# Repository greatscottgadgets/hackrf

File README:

This repository contains hardware designs and software for HackRF, a project to
produce a low cost, open source software radio platform.

https://github.com/wishi/hackrf/raw/master/doc/lemonAndjelly.jpeg

principal author: Michael Ossmann <mike@ossmann.com>
source repository: https://github.com/mossmann/hackrf

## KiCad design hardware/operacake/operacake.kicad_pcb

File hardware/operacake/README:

Copyright 2012 - 2016 Great Scott Gadgets

These files are part of HackRF.

This is a free hardware design; you can redistribute it and/or modify
it under the terms of the GNU General Public License as published by
the Free Software Foundation; either version 2, or (at your option)
any later version.

This design is distributed in the hope that it will be useful,
but WITHOUT ANY WARRANTY; without even the implied warranty of
MERCHANTABILITY or FITNESS FOR A PARTICULAR PURPOSE.  See the
GNU General Public License for more details.

You should have received a copy of the GNU General Public License
along with this design; see the file COPYING.  If not, write to
the Free Software Foundation, Inc., 51 Franklin Street,
Boston, MA 02110-1301, USA.

Opera Cake is an RF switching add-on for HackRF One.

hardware notes:

Schematic and layout files were designed in KiCad, an open source electronic
design automation package.

order of copper layers:
    Copper 1:  C1F (front)
    Copper 2:  C2
    Copper 3:  C3
    Copper 4:  C4B (back)

PCB description: 4 layer PCB 0.0646 in
    Copper       1:  1 oz copper (1.4 mil)
    Dielectric 1-2:  6.7 mil prepreg
    Copper       2:  0.5 oz copper (0.7 mil)
    Dielectric 2-3:  47 mil core
    Copper       3:  0.5 oz copper (0.7 mil)
    Dielectric 3-4:  6.7 mil prepreg
    Copper       4:  1 oz copper (1.4 mil)

FR408 or similar substrate with Er=3.66 (+/- 0.1)
double side solder mask green
double side silkscreen white
6 mil min trace width and
6 mil min isolation

PCBs of this specification are available from OSH Park.

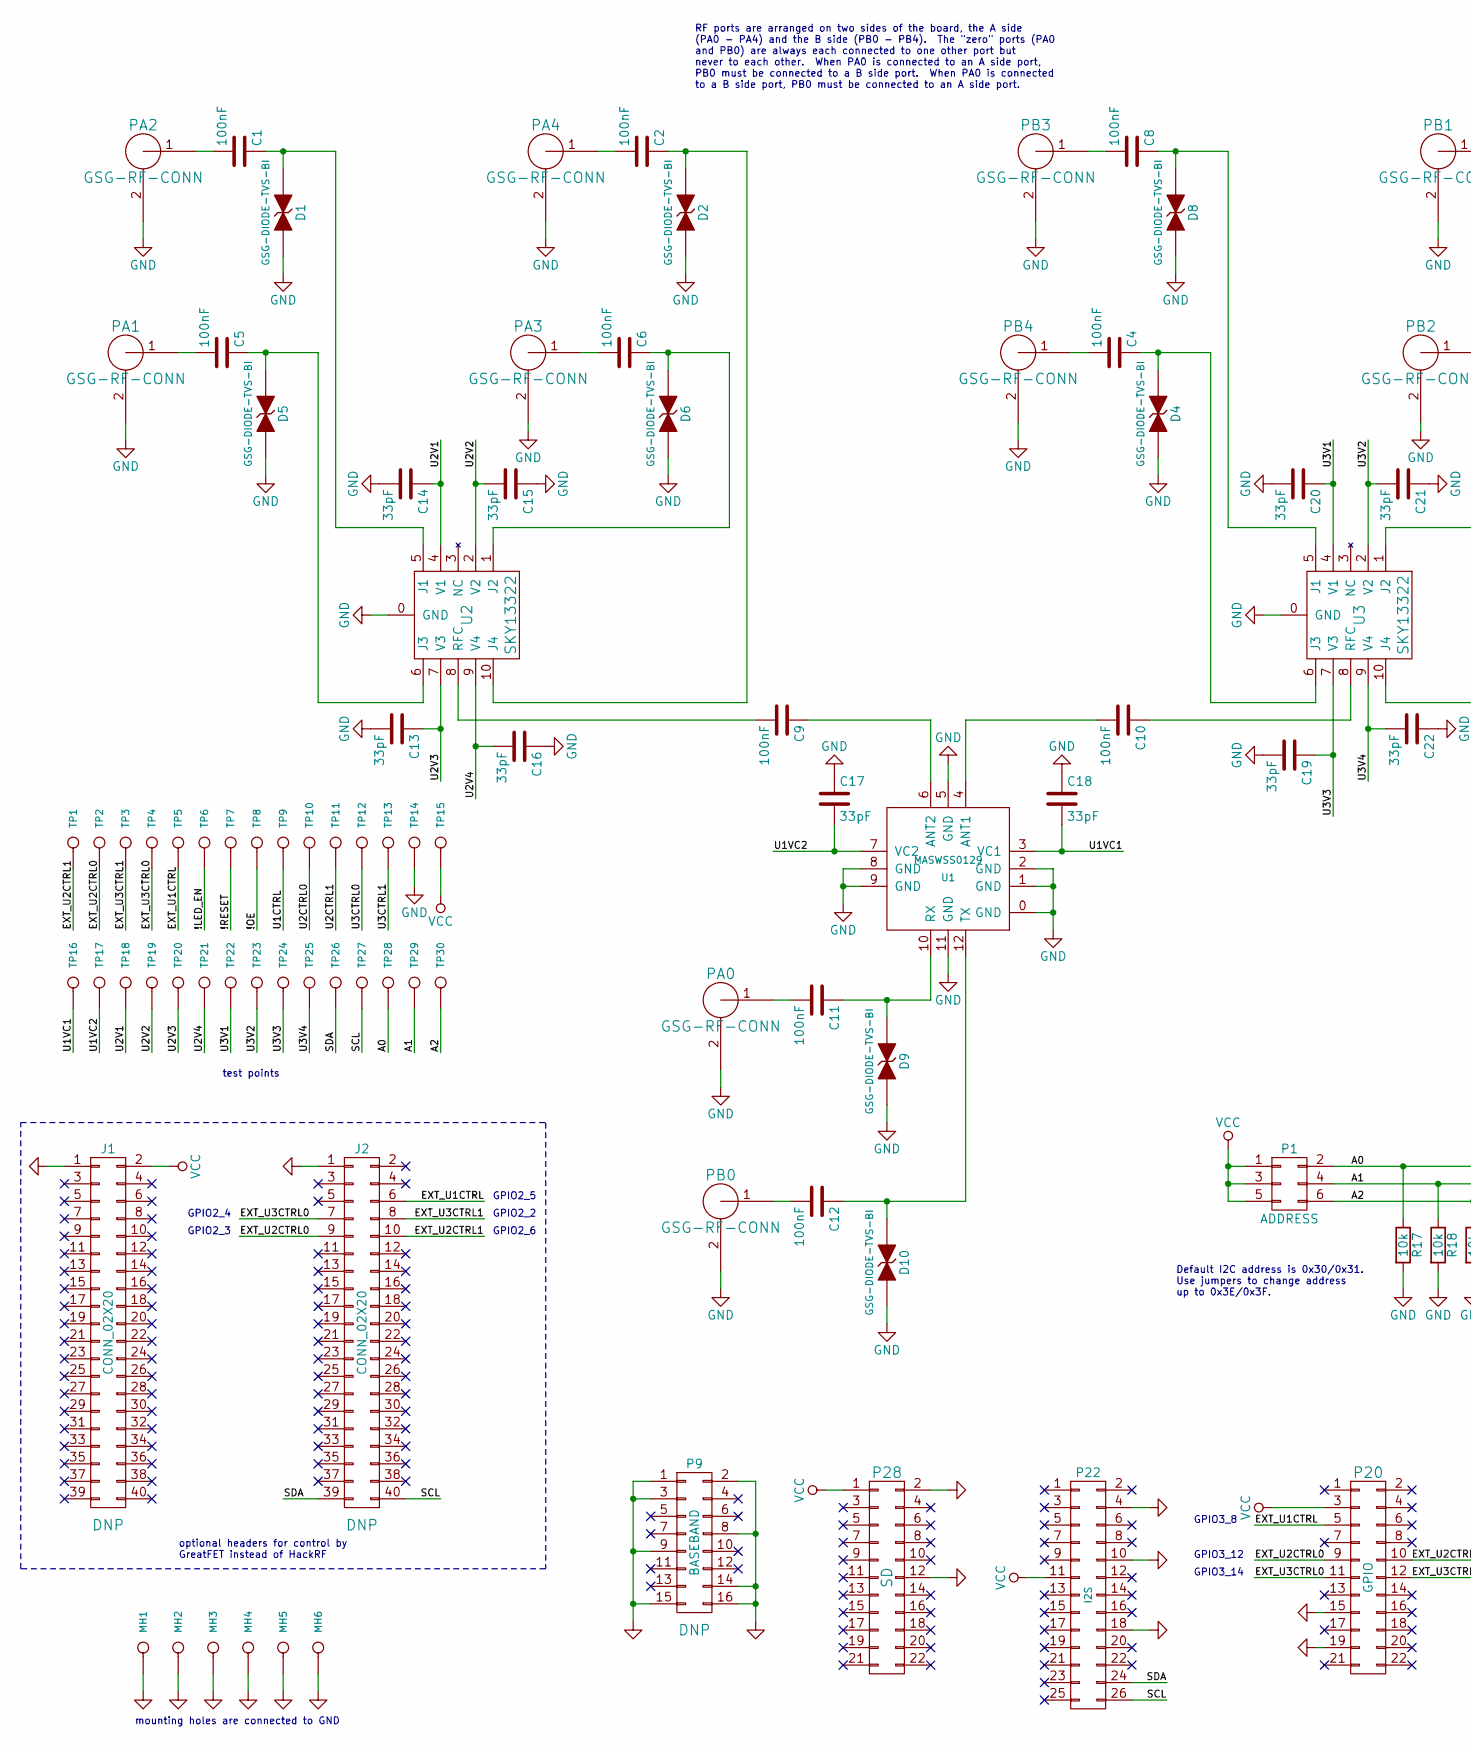
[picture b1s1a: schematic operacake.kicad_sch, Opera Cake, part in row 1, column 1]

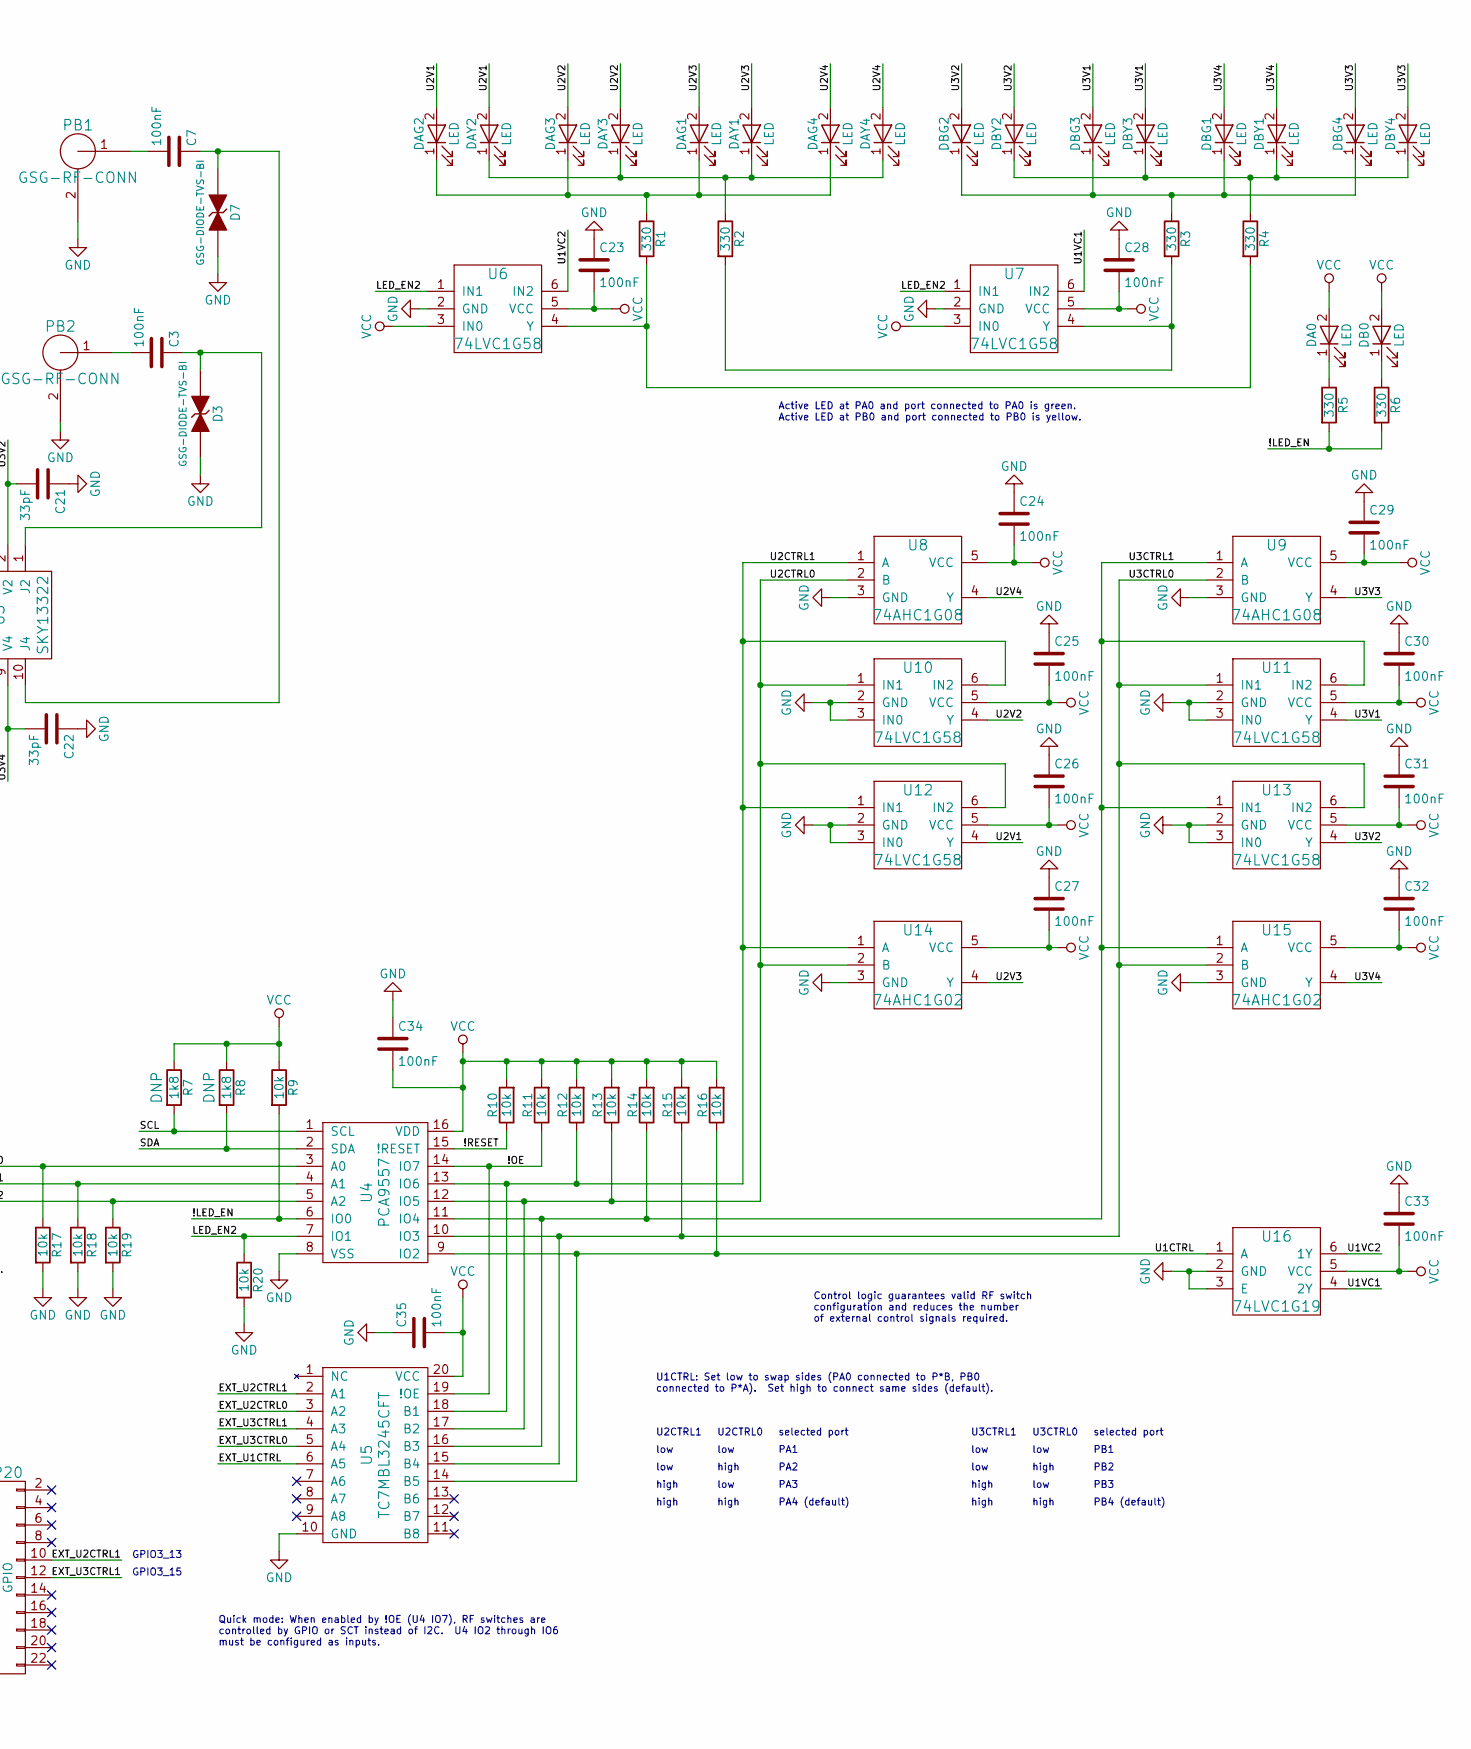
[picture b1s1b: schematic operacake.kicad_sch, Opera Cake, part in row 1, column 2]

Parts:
C1, C2, C3, C4, C5, C6, C7, C8, C9, C10, C11, C12, C23, C24, C25, C26, C27, C28, C29, C30, C31, C32, C33, C34, C35: 100nF; 0402; Part Number GRM155R61A104KA01D
C13, C14, C15, C16, C17, C18, C19, C20, C21, C22: 33pF; 0402; Part Number GRM1555C1H330JA01D
D1, D2, D3, D4, D5, D6, D7, D8, D9, D10: GSG-DIODE-TVS-BI; 0402; Part Number LXES15AAA1-153
DA0: LED; 0603D; Part Number SML-LX0603GW-TR
DAG1, DAG2, DAG3, DAG4: LED; 0603D; Part Number SML-LX0603GW-TR
DAY1, DAY2, DAY3, DAY4: LED; 0603D; Part Number SML-LX0603YW-TR
DB0: LED; 0603D; Part Number SML-LX0603YW-TR
DBG1, DBG2, DBG3, DBG4: LED; 0603D; Part Number SML-LX0603GW-TR
DBY1, DBY2, DBY3, DBY4: LED; 0603D; Part Number SML-LX0603YW-TR
J1, J2: CONN_02X20; HEADER-2x20-REVERSE
MH1, MH2, MH3, MH4, MH5, MH6: MOUNTING_HOLE; HOLE126MIL-COPPER
P1: ADDRESS; HEADER-2x3; Part Number XG8T-0631
P9: BASEBAND; HEADER-2x8; Part Number SSQ-108-03-G-D
P20: GPIO; HEADER-2x11; Part Number SSQ-111-03-G-D
P22: I2S; HEADER-2x13; Part Number SSQ-113-03-G-D
P28: SD; HEADER-2x11; Part Number SSQ-111-03-G-D
PA0, PA1, PA2, PA3, PA4: GSG-RF-CONN; GSG-SMA-73251-2120; Part Number 73251-2121
PB0, PB1, PB2, PB3, PB4: GSG-RF-CONN; GSG-SMA-73251-2120; Part Number 73251-2121
R1, R2, R3, R4, R5, R6: 330; 0603; Part Number RMCF0603JT330R
R7, R8: 1k8; 0603
R9, R10, R11, R12, R13, R14, R15, R16, R17, R18, R19, R20: 10k; 0603; Part Number ERJ-3GEYJ103V
TP1, TP2, TP3, TP4, TP5, TP6, TP7, TP8, TP9, TP10, TP11, TP12, TP13, TP14, TP15, TP16, TP17, TP18, TP19, TP20, TP21, TP22, TP23, TP24, TP25, TP26, TP27, TP28, TP29, TP30: CONN_1; TESTPOINT-50MIL
U1: MASWSS0129; QFN12-3; Part Number MASWSS0129TR-3000
U2, U3: SKY13322; SKY13322-375LF; Part Number SKY13322-375LF
U4: PCA9557; TSSOP16; Part Number PCA9557PW,118
U5: TC7MBL3245CFT; TSSOP20; Part Number TC7MBL3245CFT(EL)
U6, U7, U10, U11, U12, U13: 74LVC1G58; SOT363; Part Number 74LVC1G58DW-7
U8, U9: 74AHC1G08; SOT353-1; Part Number 74AHC1G08SE-7
U14, U15: 74AHC1G02; SOT353-1; Part Number 74AHC1G02SE-7
U16: 74LVC1G19; SOT363; Part Number 74LVC1G19GW,125

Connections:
/!LED_EN: R5.2, R6.2, R9.2, TP6.1, U4.6 (IO0)
/!OE: R11.1, TP8.1, U4.14 (IO7), U5.19 (!OE)
/!RESET: R10.1, TP7.1, U4.15 (!RESET)
/A0: P1.2, R17.1, TP28.1, U4.3 (A0)
/A1: P1.4, R18.1, TP29.1, U4.4 (A1)
/A2: P1.6, R19.1, TP30.1, U4.5 (A2)
/EXT_U1CTRL: J2.6, P20.5, TP5.1, U5.6 (A5)
/EXT_U2CTRL0: J2.9, P20.9, TP2.1, U5.3 (A2)
/EXT_U2CTRL1: J2.10, P20.10, TP1.1, U5.2 (A1)
/EXT_U3CTRL0: J2.7, P20.11, TP4.1, U5.5 (A4)
/EXT_U3CTRL1: J2.8, P20.12, TP3.1, U5.4 (A3)
/LED_EN2: R20.1, U4.7 (IO1), U6.1 (IN1), U7.1 (IN1)
/SCL: J2.40, P22.26, R7.2, TP27.1, U4.1 (SCL)
/SDA: J2.39, P22.24, R8.2, TP26.1, U4.2 (SDA)
/U1CTRL: R16.1, TP9.1, U4.9 (IO2), U5.14 (B5), U16.1 (A)
/U1VC1: C18.2, TP16.1, U1.3 (VC1), U7.6 (IN2), U16.4 (2Y)
/U1VC2: C17.2, TP17.1, U1.7 (VC2), U6.6 (IN2), U16.6 (1Y)
/U2CTRL0: R13.1, TP10.1, U4.12 (IO5), U5.17 (B2), U8.2 (B), U10.1 (IN1), U12.6 (IN2), U14.2 (B)
/U2CTRL1: R12.1, TP11.1, U4.13 (IO6), U5.18 (B1), U8.1 (A), U10.6 (IN2), U12.1 (IN1), U14.1 (A)
/U2V1: C14.1, DAG2.2 (A), DAY2.2 (A), TP18.1, U2.4 (V1), U12.4 (Y)
/U2V2: C15.2, DAG3.2 (A), DAY3.2 (A), TP19.1, U2.2 (V2), U10.4 (Y)
/U2V3: C13.1, DAG1.2 (A), DAY1.2 (A), TP20.1, U2.7 (V3), U14.4 (Y)
/U2V4: C16.2, DAG4.2 (A), DAY4.2 (A), TP21.1, U2.9 (V4), U8.4 (Y)
/U3CTRL0: R15.1, TP12.1, U4.10 (IO3), U5.15 (B4), U9.2 (B), U11.1 (IN1), U13.6 (IN2), U15.2 (B)
/U3CTRL1: R14.1, TP13.1, U4.11 (IO4), U5.16 (B3), U9.1 (A), U11.6 (IN2), U13.1 (IN1), U15.1 (A)
/U3V1: C20.1, DBG3.2 (A), DBY3.2 (A), TP22.1, U3.4 (V1), U11.4 (Y)
/U3V2: C21.2, DBG2.2 (A), DBY2.2 (A), TP23.1, U3.2 (V2), U13.4 (Y)
/U3V3: C19.1, DBG4.2 (A), DBY4.2 (A), TP24.1, U3.7 (V3), U9.4 (Y)
/U3V4: C22.2, DBG1.2 (A), DBY1.2 (A), TP25.1, U3.9 (V4), U15.4 (Y)
GND: C13.2, C14.2, C15.1, C16.1, C17.1, C18.1, C19.2, C20.2, C21.1, C22.1, C23.1, C24.1, C25.1, C26.1, C27.1, C28.1, C29.1, C30.1, C31.1, C32.1, C33.1, C34.1, C35.1, D1.2 (K), D2.2 (K), D3.2 (K), D4.2 (K), D5.2 (K), D6.2 (K), D7.2 (K), D8.2 (K), D9.2 (K), D10.2 (K), J1.1, J2.1, MH1.1, MH2.1, MH3.1, MH4.1, MH5.1, MH6.1, P9.1, P9.2, P9.3, P9.8, P9.9, P9.14, P9.15, P9.16, P20.15, P20.19, P22.4, P22.10, P22.18, P28.2, P28.12, PA0.2 (GND), PA1.2 (GND), PA2.2 (GND), PA3.2 (GND), PA4.2 (GND), PB0.2 (GND), PB1.2 (GND), PB2.2 (GND), PB3.2 (GND), PB4.2 (GND), R17.2, R18.2, R19.2, R20.2, TP14.1, U1.0 (GND), U1.1 (GND), U1.2 (GND), U1.5 (GND), U1.8 (GND), U1.9 (GND), U1.11 (GND), U2.0 (GND), U3.0 (GND), U4.8 (VSS), U5.10 (GND), U6.2 (GND), U7.2 (GND), U8.3 (GND), U9.3 (GND), U10.2 (GND), U10.3 (IN0), U11.2 (GND), U11.3 (IN0), U12.2 (GND), U12.3 (IN0), U13.2 (GND), U13.3 (IN0), U14.3 (GND), U15.3 (GND), U16.2 (GND), U16.3 (E)
unnamed: C1.1, D1.1 (A), U2.5 (J1)
unnamed: C1.2, PA2.1 (RF)
unnamed: C2.1, D2.1 (A), U2.10 (J4)
unnamed: C2.2, PA4.1 (RF)
unnamed: C3.1, D3.1 (A), U3.1 (J2)
unnamed: C3.2, PB2.1 (RF)
unnamed: C4.1, D4.1 (A), U3.6 (J3)
unnamed: C4.2, PB4.1 (RF)
unnamed: C5.1, D5.1 (A), U2.6 (J3)
unnamed: C5.2, PA1.1 (RF)
unnamed: C6.1, D6.1 (A), U2.1 (J2)
unnamed: C6.2, PA3.1 (RF)
unnamed: C7.1, D7.1 (A), U3.10 (J4)
unnamed: C7.2, PB1.1 (RF)
unnamed: C8.1, D8.1 (A), U3.5 (J1)
unnamed: C8.2, PB3.1 (RF)
unnamed: C9.1, U1.6 (ANT2)
unnamed: C9.2, U2.8 (RFC)
unnamed: C10.1, U3.8 (RFC)
unnamed: C10.2, U1.4 (ANT1)
unnamed: C11.1, D9.1 (A), U1.10 (RX)
unnamed: C11.2, PA0.1 (RF)
unnamed: C12.1, D10.1 (A), U1.12 (TX)
unnamed: C12.2, PB0.1 (RF)
unnamed: DA0.1 (K), R5.1
unnamed: DAG1.1 (K), DAG2.1 (K), DAG3.1 (K), DAG4.1 (K), R1.1
unnamed: DAY1.1 (K), DAY2.1 (K), DAY3.1 (K), DAY4.1 (K), R2.1
unnamed: DB0.1 (K), R6.1
unnamed: DBG1.1 (K), DBG2.1 (K), DBG3.1 (K), DBG4.1 (K), R3.1
unnamed: DBY1.1 (K), DBY2.1 (K), DBY3.1 (K), DBY4.1 (K), R4.1
unnamed: R1.2, R4.2, U6.4 (Y)
unnamed: R2.2, R3.2, U7.4 (Y)
VCC: C23.2, C24.2, C25.2, C26.2, C27.2, C28.2, C29.2, C30.2, C31.2, C32.2, C33.2, C34.2, C35.2, DA0.2 (A), DB0.2 (A), J1.2, P1.1, P1.3, P1.5, P20.3, P22.11, P28.1, R7.1, R8.1, R9.1, R10.2, R11.2, R12.2, R13.2, R14.2, R15.2, R16.2, TP15.1, U4.16 (VDD), U5.20 (VCC), U6.3 (IN0), U6.5 (VCC), U7.3 (IN0), U7.5 (VCC), U8.5 (VCC), U9.5 (VCC), U10.5 (VCC), U11.5 (VCC), U12.5 (VCC), U13.5 (VCC), U14.5 (VCC), U15.5 (VCC), U16.5 (VCC)

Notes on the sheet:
PB2
selected port
mounting holes are connected to GND
GPIO2_4
RF ports are arranged on two sides of the board, the A side (PA0 - PA4) and the B side (PB0 - PB4). The "zero" ports (PA0 and PB0) are always each connected to one other port but never to each other. When PA0 is connected to an A side port, PB0 must be connected to a B side port. When PA0 is connec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
GPIO3_14
low
high
GPIO3_8
PA2
U3CTRL0
Quick mode: When enabled by !OE (U4 IO7), RF switches are controlled by GPIO or SCT instead of I2C. U4 IO2 through IO6 must be configured as inputs.
PA3
GPIO2_6
PB4 (default)
U3CTRL1
GPIO3_15
Control logic guarantees valid RF switch configuration and reduces the number of external control signals required.
GPIO3_12
PB1
GPIO3_13
Default I2C address is 0x30/0x31. Use jumpers to change address up to 0x3E/0x3F.
GPIO2_2
test points
GPIO2_3
optional headers for control by GreatFET instead of HackRF
U1CTRL: Set low to swap sides (PA0 connected to P*B, PB0 connected to P*A). Set high to connect same sides (default).
PA4 (default)
PB3
GPIO2_5
Active LED at PA0 and port connected to PA0 is green. Active LED at PB0 and port connected to PB0 is yellow.
PA1
U2CTRL1
U2CTRL0

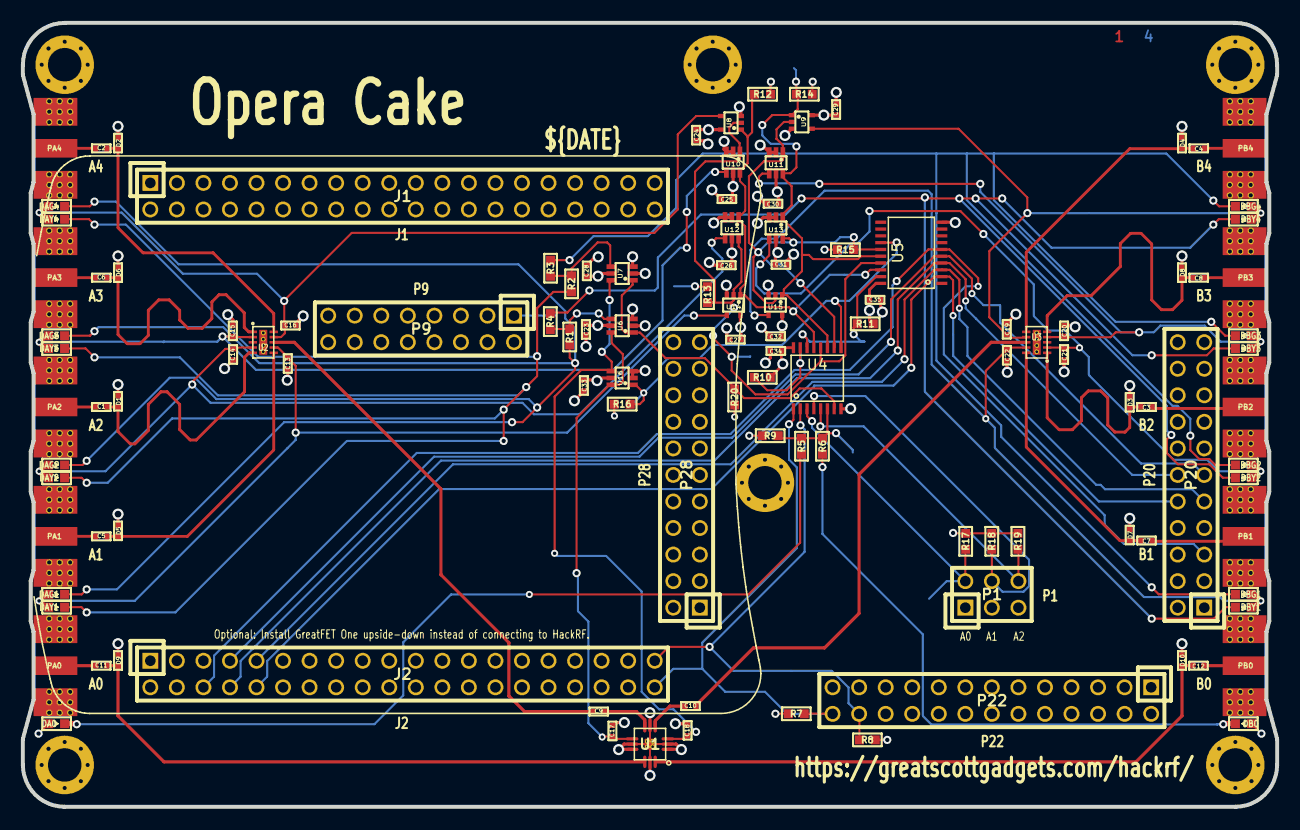
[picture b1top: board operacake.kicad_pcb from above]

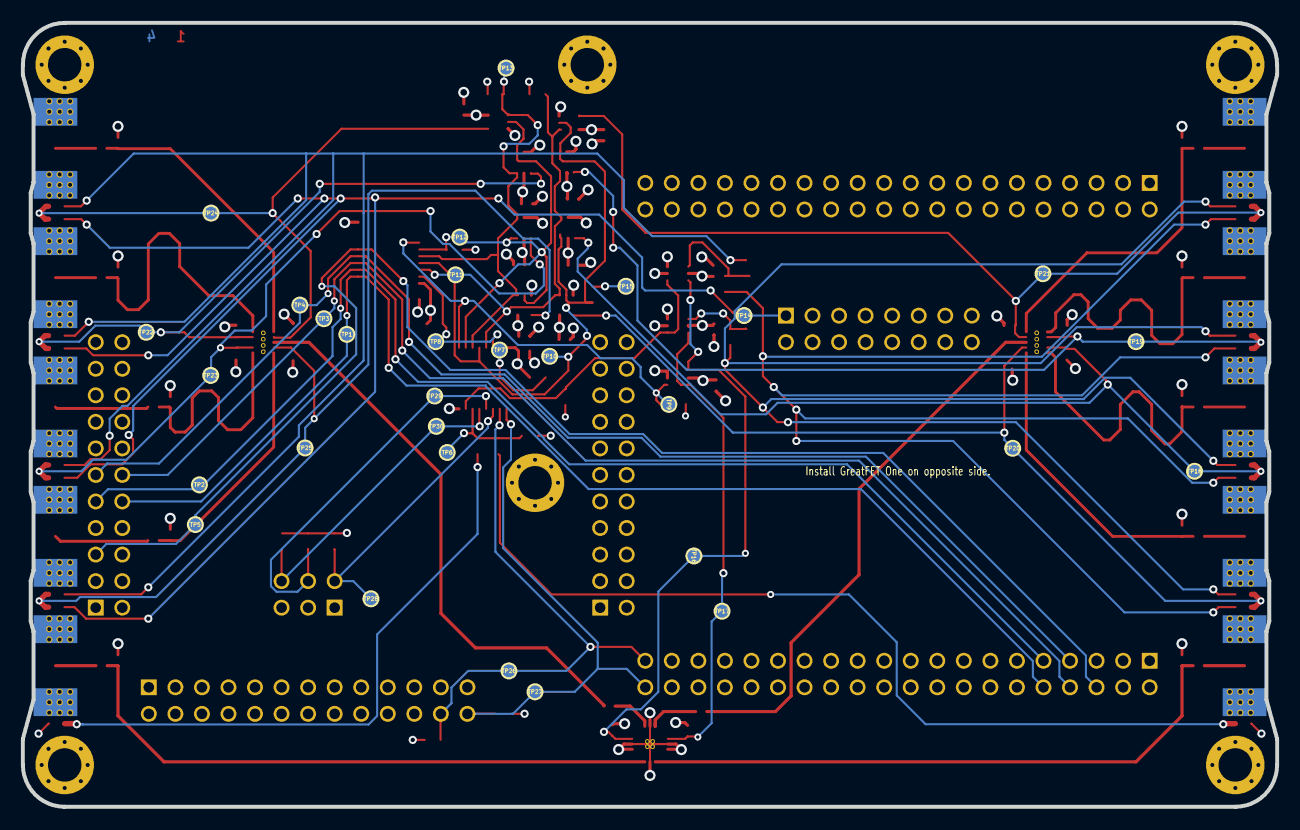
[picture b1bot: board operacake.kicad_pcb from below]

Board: 4 copper layers, 120.0 x 75.0 mm, 152 parts (30 on the bottom side), 63 nets.

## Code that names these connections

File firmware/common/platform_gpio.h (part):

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	gpio_t gpio_3v3aux_enable_n;
#endif

	/* MAX283x GPIO (XCVR_CTL / CS_XCVR) PinMux */
	gpio_t max283x_select;
	gpio_t max283x_enable;
	gpio_t max283x_rx_enable;
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	gpio_t max2831_ld;
#endif

	/* MAX5864 SPI chip select (AD_CS / CS_AD) GPIO PinMux */
	gpio_t max5864_select;

	/* RF supply (VAA) control */
	gpio_t vaa_disable;
#ifdef IS_RAD1O
	gpio_t vaa_enable;
#endif

	/* W25Q80BV Flash */
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#ifdef IS_HACKRF_ONE
	gpio_t hp;
	gpio_t lp;
	gpio_t tx_mix_bp;
	gpio_t no_mix_bypass;
	gpio_t rx_mix_bp;
	gpio_t tx;
	gpio_t mix_bypass;
	gpio_t rx;
	gpio_t no_tx_amp_pwr;
	gpio_t amp_bypass;
	gpio_t rx_amp;
	gpio_t no_rx_amp_pwr;
	gpio_t h1r9_no_ant_pwr; // HACKRF_ONE r9
	gpio_t h1r9_rx;         // HACKRF_ONE r9
#endif
#ifdef IS_H1_OR_RAD1O
	gpio_t tx_amp;
#endif
#ifdef IS_RAD1O
	gpio_t tx_rx_n;
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#endif

	/* CPLD JTAG interface GPIO pins, FPGA config pins in Praline */
	gpio_t cpld_tck;
#ifdef IS_NOT_PRALINE
	gpio_t cpld_tdo;
	gpio_t cpld_tms;
	gpio_t cpld_tdi;
#endif
#ifdef IS_EXPANSION_COMPATIBLE
	gpio_t cpld_pp_tms;
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static const struct gpio GPIO3_5 = GPIO(3, 5);
static const struct gpio GPIO3_6 = GPIO(3, 6);
static const struct gpio GPIO3_7 = GPIO(3, 7);
static const struct gpio GPIO3_8 = GPIO(3, 8);
static const struct gpio GPIO3_9 = GPIO(3, 9);
static const struct gpio GPIO3_10 = GPIO(3, 10);
static const struct gpio GPIO3_11 = GPIO(3, 11);
static const struct gpio GPIO3_12 = GPIO(3, 12);
static const struct gpio GPIO3_13 = GPIO(3, 13);
static const struct gpio GPIO3_14 = GPIO(3, 14);
static const struct gpio GPIO3_15 = GPIO(3, 15);

static const struct gpio GPIO4_0 = GPIO(4, 0);
static const struct gpio GPIO4_1 = GPIO(4, 1);
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
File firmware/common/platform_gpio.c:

/*
 * Copyright 2012-2026 Great Scott Gadgets <info@greatscottgadgets.com>
 *
 * This file is part of HackRF.
 *
 * This program is free software; you can redistribute it and/or modify
 * it under the terms of the GNU General Public License as published by
 * the Free Software Foundation; either version 2, or (at your option)
 * any later version.
 *
 * This program is distributed in the hope that it will be useful,
 * but WITHOUT ANY WARRANTY; without even the implied warranty of
 * MERCHANTABILITY or FITNESS FOR A PARTICULAR PURPOSE.  See the
 * GNU General Public License for more details.
 *
 * You should have received a copy of the GNU General Public License
 * along with this program; see the file COPYING.  If not, write to
 * the Free Software Foundation, Inc., 51 Franklin Street,
 * Boston, MA 02110-1301, USA.
 */

#include "platform_gpio.h"

#include <stddef.h>

#include "platform_detect.h"

// clang-format off

__attribute__((section(".rtconfig")))
const platform_gpio_t* platform_gpio(void)
{
	static const platform_gpio_t* _platform_gpio = NULL;
	if (_platform_gpio != NULL) {
		return _platform_gpio;
	}

	static platform_gpio_t gpio;

	/* LEDs */
	gpio.led[0] = &GPIO2_1;
	gpio.led[1] = &GPIO2_2;
	gpio.led[2] = &GPIO2_8;
#ifdef IS_RAD1O
	if (IS_RAD1O) {
		gpio.led[3] = &GPIO5_26;
	}
#endif
#ifdef IS_PRALINE
	if (IS_PRALINE) {
		gpio.led[3] = &GPIO4_6;
	}
#endif

	/* Power Supply Control */
#ifdef IS_PRALINE
	if (IS_PRALINE) {
		gpio.gpio_1v2_enable      = &GPIO4_7;
		gpio.gpio_3v3aux_enable_n = &GPIO5_15;
	}
#endif
#ifdef IS_NOT_PRALINE
	if (IS_NOT_PRALINE) {
		gpio.gpio_1v8_enable      = &GPIO3_6;
	}
#endif

	/* MAX283x GPIO (XCVR_CTL / CS_XCVR) PinMux */
#ifdef IS_PRALINE
	if (IS_PRALINE) {
		gpio.max283x_select    = &GPIO6_28;
		gpio.max283x_enable    = &GPIO7_1;
		gpio.max283x_rx_enable = &GPIO7_2;
		gpio.max2831_rxhp      = &GPIO6_29;
		gpio.max2831_ld        = &GPIO4_11;
	}
#endif
#ifdef IS_NOT_PRALINE
	if (IS_NOT_PRALINE) {
		gpio.max283x_select    = &GPIO0_15;
		gpio.max283x_enable    = &GPIO2_6;
		gpio.max283x_rx_enable = &GPIO2_5;
		gpio.max283x_tx_enable = &GPIO2_4;
	}
#endif

	/* MAX5864 SPI chip select (AD_CS / CS_AD) GPIO PinMux */
#ifdef IS_PRALINE
	if (IS_PRALINE) {
		gpio.max5864_select    = &GPIO6_30;
	}
#endif
#ifdef IS_NOT_PRALINE
	if (IS_NOT_PRALINE) {
		gpio.max5864_select    = &GPIO2_7;
	}
#endif

	/* RF supply (VAA) control */
#ifdef IS_HACKRF_ONE
	if (IS_HACKRF_ONE) {
		gpio.vaa_disable       = &GPIO2_9;
	}
#endif
#ifdef IS_PRALINE
	if (IS_PRALINE) {
		gpio.vaa_disable       = &GPIO4_1;
	}
#endif
#ifdef IS_RAD1O
	if (IS_RAD1O) {
		gpio.vaa_enable        = &GPIO2_9;
	}
#endif

	/* W25Q80BV Flash */
	gpio.w25q80bv_hold     = &GPIO1_14;
	gpio.w25q80bv_wp       = &GPIO1_15;
	gpio.w25q80bv_select   = &GPIO5_11;

	/* RF switch control */
#ifdef IS_HACKRF_ONE
	if (IS_HACKRF_ONE) {
		gpio.hp              = &GPIO2_0;
		gpio.lp              = &GPIO2_10;
		gpio.tx_mix_bp       = &GPIO2_11;
		gpio.no_mix_bypass   = &GPIO1_0;
		gpio.rx_mix_bp       = &GPIO2_12;
		gpio.tx_amp          = &GPIO2_15;
		gpio.tx              = &GPIO5_15;
		gpio.mix_bypass      = &GPIO5_16;
		gpio.rx              = &GPIO5_5;
		gpio.no_tx_amp_pwr   = &GPIO3_5;
		gpio.amp_bypass      = &GPIO0_14;
		gpio.rx_amp          = &GPIO1_11;
		gpio.no_rx_amp_pwr   = &GPIO1_12;
#ifdef IS_H1_R9
		if (IS_H1_R9) {
			gpio.h1r9_rx         = &GPIO0_7;
			gpio.h1r9_no_ant_pwr = &GPIO2_4;
		}
#endif
	}
#endif
#ifdef IS_RAD1O
	if (IS_RAD1O) {
		gpio.tx_rx_n         = &GPIO1_11;
		gpio.tx_rx           = &GPIO0_14;
		gpio.by_mix          = &GPIO1_12;
		gpio.by_mix_n        = &GPIO2_10;
		gpio.by_amp          = &GPIO1_0;
		gpio.by_amp_n        = &GPIO5_5;
		gpio.mixer_en        = &GPIO5_16;
		gpio.low_high_filt   = &GPIO2_11;
		gpio.low_high_filt_n = &GPIO2_12;
		gpio.tx_amp          = &GPIO2_15;
		gpio.rx_lna          = &GPIO5_15;
	}
#endif
#ifdef IS_PRALINE
	if (IS_PRALINE) {
		gpio.tx_en           = &GPIO3_4;
		gpio.mix_en_n        = &GPIO3_2;
		gpio.mix_en_n_r1_0   = &GPIO5_6;
		gpio.lpf_en          = &GPIO4_8;
		gpio.rf_amp_en       = &GPIO4_9;
		gpio.ant_bias_en_n   = &GPIO1_12;
	}
#endif

	/* CPLD JTAG interface GPIO pins_FPGA config pins in Praline */
	gpio.cpld_tck                  = &GPIO3_0;
#ifdef IS_PRALINE
	if (IS_PRALINE) {
		gpio.fpga_cfg_creset       = &GPIO2_11;
		gpio.fpga_cfg_cdone        = &GPIO5_14;
		gpio.fpga_cfg_spi_cs       = &GPIO2_10;
	}
#endif
#ifdef IS_NOT_PRALINE
	if (IS_NOT_PRALINE) {
		gpio.cpld_tdo              = &GPIO5_18;
	}
#endif
#ifdef IS_H1_OR_RAD1O
	if (IS_H1_OR_RAD1O) {
		gpio.cpld_tms          = &GPIO3_4;
		gpio.cpld_tdi          = &GPIO3_1;
	}
#endif
#ifdef IS_JAWBREAKER
	if (IS_JAWBREAKER) {
		gpio.cpld_tms          = &GPIO3_1;
		gpio.cpld_tdi          = &GPIO3_4;
	}
#endif
#ifdef IS_EXPANSION_COMPATIBLE
	if (IS_EXPANSION_COMPATIBLE) {
		gpio.cpld_pp_tms       = &GPIO1_1;
		gpio.cpld_pp_tdo       = &GPIO1_8;
	}
#endif

	/* Other CPLD interface GPIO pins */
#ifdef IS_NOT_PRALINE
	if (IS_NOT_PRALINE) {
		gpio.trigger_enable = &GPIO5_12;
	}
#endif
	gpio.q_invert           = &GPIO0_13;

	/* RFFC5071 GPIO serial interface PinMux */
#ifdef IS_NOT_RAD1O
	if (IS_NOT_RAD1O) {
		gpio.rffc5072_select = &GPIO2_13;
		gpio.rffc5072_clock  = &GPIO5_6;
		gpio.rffc5072_data   = &GPIO3_3;
		gpio.rffc5072_reset  = &GPIO2_14;
	}
#endif
#ifdef IS_RAD1O
	if (IS_RAD1O) {
		gpio.vco_ce        = &GPIO2_13;
		gpio.vco_sclk      = &GPIO5_6;
		gpio.vco_sdata     = &GPIO3_3;
		gpio.vco_le        = &GPIO2_14;
		gpio.vco_mux       = &GPIO5_25;
		gpio.synt_rfout_en = &GPIO3_5;
	}
#endif
#ifdef IS_PRALINE
	if (IS_PRALINE) {
		gpio.rffc5072_select = &GPIO2_13;
		gpio.rffc5072_clock  = &GPIO5_18;
		gpio.rffc5072_data   = &GPIO4_14;
		gpio.rffc5072_reset  = &GPIO2_14;
		gpio.rffc5072_ld     = &GPIO6_25;
		gpio.rffc5072_enbl   = &GPIO4_12;
	}
#endif

	/* Praline */
#ifdef IS_PRALINE
	if (IS_PRALINE) {
		gpio.p2_ctrl0     = &GPIO7_3;
		gpio.p2_ctrl1     = &GPIO7_4;
		gpio.p1_ctrl0     = &GPIO0_14;
		gpio.p1_ctrl1     = &GPIO5_16;
		gpio.p1_ctrl2     = &GPIO3_5;
		gpio.clkin_ctrl   = &GPIO0_15;
		gpio.aa_en        = &GPIO1_7;
		gpio.trigger_in   = &GPIO6_26;
		gpio.trigger_out  = &GPIO5_6;
		gpio.pps_out      = &GPIO5_5;
	}
#endif

	/* HackRF One r9 clock control */
#ifdef IS_H1_R9
	if (IS_H1_R9) {
		gpio.h1r9_clkin_en   = &GPIO5_15;
		gpio.h1r9_clkout_en  = &GPIO0_9;
		gpio.h1r9_mcu_clk_en = &GPIO0_8;
		gpio.h1r9_1v8_enable     = &GPIO2_9;
		gpio.h1r9_vaa_disable    = &GPIO3_6;
		gpio.h1r9_trigger_enable = &GPIO5_5;
	}
#endif

	/* rad1o LCD */
#ifdef IS_RAD1O
	if (IS_RAD1O) {
		gpio.lcd_cs    = &GPIO4_12; /* P9_0 */
		gpio.lcd_bl_en = &GPIO0_8;  /* P1_1 */
		gpio.lcd_reset = &GPIO5_17; /* P9_4 */
	}
#endif

	/* Portapack */
#ifdef IS_EXPANSION_COMPATIBLE
	if (IS_EXPANSION_COMPATIBLE) {
		gpio.io_stbx = &GPIO5_0;  /* P2_0 */
		gpio.addr    = &GPIO5_1;  /* P2_1 */
		gpio.lcd_rdx = &GPIO5_4;  /* P2_4 */
		gpio.lcd_wrx = &GPIO1_10; /* P2_9 */
		gpio.dir     = &GPIO1_13; /* P2_13 */
	}
#endif

	_platform_gpio = &gpio;

	return _platform_gpio;
}

// clang-format on

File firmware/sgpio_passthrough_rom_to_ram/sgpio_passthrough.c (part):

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	/* Enable SGPIO pin outputs. */
	/****************************************************/
	SGPIO_GPIO_OENREG =
        0xFFFF;           // data: output for SGPIO0 to SGPIO15

	/*******************************************************************************/
	/* SGPIO pin 0 outputs slice A bit 0. (see Table 212. Output pin multiplexing) */
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
	/* 
		Expected: 
		SGPIO12 = MCU Freq/2
		SGPIO0  = SGPIO12/2 MHz= 51MHz (SliceD/2)
	*/

}
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/*******************************************************************************/
const u8 slice_preset_tab[16] =
{
	0,  /* Idx00 = Slice A => SGPIO0  Freq Div by 1=0 */
	8,  /* Idx01 = Slice B => SGPIO8  Freq Div by 9=8 */
	4,  /* Idx02 = Slice C => SGPIO4  Freq Div by 5=4 */
	12, /* Idx03 = Slice D => SGPIO12 Freq Div by 13=12 */
	2,  /* Idx04 = Slice E => SGPIO2 Freq Div by 3=2 */
	6,  /* Idx05 = Slice F => SGPIO6 Freq Div by 7=6 */
	10, /* Idx06 = Slice G => SGPIO10 Freq Div by 11=10 */
	14, /* Idx07 = Slice H => SGPIO14 Freq Div by 15=14 */
	1,  /* Idx08 = Slice I => SGPIO1 Freq Div by 2=1 */
	3,  /* Idx09 = Slice J => SGPIO3 Freq Div by 4=3 */
	5,  /* Idx10 = Slice K => SGPIO5 Freq Div by 6=5 */
	7,  /* Idx11 = Slice L => SGPIO7 Freq Div by 8=7 */
	9,  /* Idx12 = Slice M => SGPIO9 Freq Div by 10=9 */
	11, /* Idx13 = Slice N => SGPIO11 Freq Div by 12=11 */
	13, /* Idx14 = Slice O => SGPIO13 Freq Div by 14=13 */
	15  /* Idx15 = Slice P => SGPIO15 Freq Div by 16=15 */
};

void test_sgpio_all_slices(void)
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	/* Enable SGPIO pin outputs. */
	/****************************************************/
	SGPIO_GPIO_OENREG =
        0xFFFF;           // data: output for SGPIO0 to SGPIO15

	for(uint_fast8_t i=0; i<16; i++) 
	{
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		SGPIO07	= 12,75000
		SGPIO08	= 11,33333
		SGPIO09	= 10,20000
		SGPIO10	= 9,27273
		SGPIO11	= 8,50000
		SGPIO12	= 7,84615
		SGPIO13	= 7,28571
		SGPIO14	= 6,80000
		SGPIO15	= 6,37500
		TitanMKD: I have problems with my boards and this test see document Test_SGPIO0_to15.ods / Test_SGPIO0_to15.pdf
	*/
}
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		SGPIO_OUT_MUX_CFG(i) = (0L << 4) | (4L << 0);
	}

	// Enable SGPIO pin outputs (SGPIO0 to 15).
	SGPIO_GPIO_OENREG = 0xFFFF;

	/* Set values for SGPIO0 to 15 */
	while (1)
	{
		// 750KHz => 272 cycles
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	enable_1v8_power();
	cpu_clock_init();
	ssp1_init();
	gpio_set(PORT_LED1_3, PIN_LED1);

	//test_sgpio_sliceA_D();
	test_sgpio_interface();
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
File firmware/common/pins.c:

/*
 * Copyright 2012-2026 Great Scott Gadgets <info@greatscottgadgets.com>
 * Copyright 2012 Jared Boone <jared@sharebrained.com>
 * Copyright 2013 Benjamin Vernoux <titanmkd@gmail.com>
 *
 * This file is part of HackRF.
 *
 * This program is free software; you can redistribute it and/or modify
 * it under the terms of the GNU General Public License as published by
 * the Free Software Foundation; either version 2, or (at your option)
 * any later version.
 *
 * This program is distributed in the hope that it will be useful,
 * but WITHOUT ANY WARRANTY; without even the implied warranty of
 * MERCHANTABILITY or FITNESS FOR A PARTICULAR PURPOSE.  See the
 * GNU General Public License for more details.
 *
 * You should have received a copy of the GNU General Public License
 * along with this program; see the file COPYING.  If not, write to
 * the Free Software Foundation, Inc., 51 Franklin Street,
 * Boston, MA 02110-1301, USA.
 */

#include "pins.h"

#include <libopencm3/lpc43xx/scu.h>

#include "cpld_jtag.h"
#include "gpio.h"
#include "leds.h"
#include "mixer.h"
#include "platform_detect.h"
#include "platform_gpio.h"
#include "platform_scu.h"
#include "power.h"
#ifdef IS_PRALINE
	#include "clock_io.h"
	#include "ice40_spi.h"
#endif

void pins_shutdown(void)
{
	/* Configure all GPIO as Input (safe state) */
	gpio_init();

	/* Detect Platform */
	const platform_gpio_t* gpio = platform_gpio();
	const platform_scu_t* scu = platform_scu();

	/* TDI and TMS pull-ups are required in all JTAG-compliant devices.
	 *
	 * The HackRF CPLD is always present, so let the CPLD pull up its TDI and TMS.
	 *
	 * The PortaPack may not be present, so pull up the PortaPack TMS pin from the
	 * microcontroller.
	 *
	 * TCK is recommended to be held low, so use microcontroller pull-down.
	 *
	 * TDO is undriven except when in Shift-IR or Shift-DR phases.
	 * Use the microcontroller to pull down to keep from floating.
	 *
	 * LPC43xx pull-up and pull-down resistors are approximately 53K.
	 */
#ifdef IS_EXPANSION_COMPATIBLE
	if (IS_EXPANSION_COMPATIBLE) {
		scu_pinmux(scu->PINMUX_PP_TMS, SCU_GPIO_PUP | SCU_CONF_FUNCTION0);
		scu_pinmux(scu->PINMUX_PP_TDO, SCU_GPIO_PDN | SCU_CONF_FUNCTION0);
	}
#endif
	scu_pinmux(scu->PINMUX_CPLD_TCK, SCU_GPIO_PDN | SCU_CONF_FUNCTION0);
#ifdef IS_NOT_PRALINE
	if (IS_NOT_PRALINE) {
		scu_pinmux(scu->PINMUX_CPLD_TMS, SCU_GPIO_NOPULL | SCU_CONF_FUNCTION0);
		scu_pinmux(scu->PINMUX_CPLD_TDI, SCU_GPIO_NOPULL | SCU_CONF_FUNCTION0);
		scu_pinmux(scu->PINMUX_CPLD_TDO, SCU_GPIO_PDN | SCU_CONF_FUNCTION4);
	}
#endif

	/* Configure SCU Pin Mux as GPIO */
	scu_pinmux(scu->PINMUX_LED1, SCU_GPIO_NOPULL);
	scu_pinmux(scu->PINMUX_LED2, SCU_GPIO_NOPULL);
	scu_pinmux(scu->PINMUX_LED3, SCU_GPIO_NOPULL);
#ifdef IS_RAD1O
	if (IS_RAD1O) {
		scu_pinmux(scu->PINMUX_LED4, SCU_GPIO_NOPULL | SCU_CONF_FUNCTION4);
	}
#endif
#ifdef IS_PRALINE
	if (IS_PRALINE) {
		scu_pinmux(scu->PINMUX_LED4, SCU_GPIO_NOPULL | SCU_CONF_FUNCTION0);
	}
#endif

	/* Configure USB indicators */
#ifdef IS_JAWBREAKER
	if (IS_JAWBREAKER) {
		scu_pinmux(scu->PINMUX_USB_LED0, SCU_CONF_FUNCTION3);
		scu_pinmux(scu->PINMUX_USB_LED1, SCU_CONF_FUNCTION3);
	}
#endif

#ifdef IS_PRALINE
	if (IS_PRALINE) {
		disable_1v2_power();
		disable_3v3aux_power();
		gpio_output(gpio->gpio_1v2_enable);
		gpio_output(gpio->gpio_3v3aux_enable_n);
		scu_pinmux(scu->PINMUX_EN1V2, SCU_GPIO_FAST | SCU_CONF_FUNCTION0);
		scu_pinmux(scu->PINMUX_EN3V3_AUX_N, SCU_GPIO_FAST | SCU_CONF_FUNCTION4);
	}
#endif

#ifdef IS_NOT_PRALINE
	if (IS_NOT_PRALINE) {
		disable_1v8_power();
	#ifdef IS_H1_R9
		if (IS_H1_R9) {
			gpio_output(gpio->h1r9_1v8_enable);
			scu_pinmux(scu->H1R9_EN1V8, SCU_GPIO_FAST | SCU_CONF_FUNCTION0);
		}
	#endif
	#ifdef IS_NOT_H1_R9
		if (IS_NOT_H1_R9) {
			gpio_output(gpio->gpio_1v8_enable);
			scu_pinmux(scu->PINMUX_EN1V8, SCU_GPIO_FAST | SCU_CONF_FUNCTION0);
		}
	#endif
	}
#endif

#ifdef IS_H1_OR_PRALINE
	if (IS_H1_OR_PRALINE) {
		/* Safe state: start with VAA turned off: */
		disable_rf_power();

		/* Configure RF power supply (VAA) switch control signal as output */
	#ifdef IS_H1_R9
		if (IS_H1_R9) {
			gpio_output(gpio->h1r9_vaa_disable);
		}
	#endif
	#ifdef IS_NOT_H1_R9
		if (IS_NOT_H1_R9) {
			gpio_output(gpio->vaa_disable);
		}
	#endif
	}
#endif

#ifdef IS_RAD1O
	if (IS_RAD1O) {
		/* Safe state: start with VAA turned off: */
		disable_rf_power();

		/* Configure RF power supply (VAA) switch control signal as output */
		gpio_output(gpio->vaa_enable);

		/* Disable unused clock outputs. They generate noise. */
		scu_pinmux(CLK0, SCU_CLK_IN | SCU_CONF_FUNCTION7);
		scu_pinmux(CLK2, SCU_CLK_IN | SCU_CONF_FUNCTION7);

		scu_pinmux(scu->PINMUX_GPIO3_10, SCU_GPIO_PDN | SCU_CONF_FUNCTION0);
		scu_pinmux(scu->PINMUX_GPIO3_11, SCU_GPIO_PDN | SCU_CONF_FUNCTION0);
	}
#endif

#ifdef IS_PRALINE
	if (IS_PRALINE) {
		scu_pinmux(scu->P2_CTRL0, scu->P2_CTRL0_PINCFG);
		scu_pinmux(scu->P2_CTRL1, scu->P2_CTRL1_PINCFG);
		scu_pinmux(scu->P1_CTRL0, scu->P1_CTRL0_PINCFG);
		scu_pinmux(scu->P1_CTRL1, scu->P1_CTRL1_PINCFG);
		scu_pinmux(scu->P1_CTRL2, scu->P1_CTRL2_PINCFG);
		scu_pinmux(scu->CLKIN_CTRL, scu->CLKIN_CTRL_PINCFG);
		scu_pinmux(scu->AA_EN, scu->AA_EN_PINCFG);
		scu_pinmux(scu->TRIGGER_IN, scu->TRIGGER_IN_PINCFG);
		scu_pinmux(scu->TRIGGER_OUT, scu->TRIGGER_OUT_PINCFG);
		scu_pinmux(scu->PPS_OUT, scu->PPS_OUT_PINCFG);
		scu_pinmux(scu->SCT_CLK, scu->SCT_CLK_PINCFG);

		scu_pinmux(scu->PINMUX_FPGA_CRESET, SCU_GPIO_PDN | SCU_CONF_FUNCTION0);
		scu_pinmux(scu->PINMUX_FPGA_CDONE, SCU_GPIO_PDN | SCU_CONF_FUNCTION4);
		scu_pinmux(scu->PINMUX_FPGA_SPI_CS, SCU_GPIO_PDN | SCU_CONF_FUNCTION0);

		scu_pinmux(scu->SSP1_CIPO, SCU_GPIO_PDN | SCU_CONF_FUNCTION0);
		scu_pinmux(scu->SSP1_COPI, SCU_GPIO_PDN | SCU_CONF_FUNCTION0);
		scu_pinmux(scu->SSP1_SCK, SCU_GPIO_PDN | SCU_CONF_FUNCTION2);

		scu_pinmux(scu->XCVR_ENABLE, SCU_GPIO_PDN | SCU_CONF_FUNCTION4);
		scu_pinmux(scu->XCVR_RXENABLE, SCU_GPIO_PDN | SCU_CONF_FUNCTION4);
		scu_pinmux(scu->XCVR_CS, SCU_GPIO_PDN | SCU_CONF_FUNCTION4);
		scu_pinmux(scu->XCVR_RXHP, SCU_GPIO_PDN | SCU_CONF_FUNCTION4);
		scu_pinmux(scu->XCVR_LD, SCU_GPIO_PDN | SCU_CONF_FUNCTION0);

		scu_pinmux(scu->MIXER_LD, SCU_GPIO_PDN | SCU_CONF_FUNCTION4);
		scu_pinmux(scu->MIXER_SCLK, SCU_GPIO_PDN | SCU_CONF_FUNCTION4);
		scu_pinmux(scu->MIXER_SDATA, SCU_GPIO_PDN | SCU_CONF_FUNCTION0);
		scu_pinmux(scu->MIXER_ENX, SCU_GPIO_PDN | SCU_CONF_FUNCTION0);
		scu_pinmux(scu->MIXER_RESETX, SCU_GPIO_PDN | SCU_CONF_FUNCTION0);
		scu_pinmux(scu->MIXER_ENBL, SCU_GPIO_PDN | SCU_CONF_FUNCTION0);

		scu_pinmux(scu->AD_CS, SCU_GPIO_PDN | SCU_CONF_FUNCTION4);

		p2_ctrl_set(P2_SIGNAL_CLK3);
		p1_ctrl_set(P1_SIGNAL_CLKIN);
		clkin_ctrl_set(CLKIN_SIGNAL_P1);

		gpio_output(gpio->p2_ctrl0);
		gpio_output(gpio->p2_ctrl1);
		gpio_output(gpio->p1_ctrl0);
		gpio_output(gpio->p1_ctrl1);
		gpio_output(gpio->p1_ctrl2);
		gpio_output(gpio->clkin_ctrl);
		gpio_output(gpio->pps_out);
		gpio_input(gpio->trigger_in);
		gpio_input(gpio->trigger_out);
		gpio_clear(gpio->fpga_cfg_spi_cs);
		gpio_output(gpio->fpga_cfg_spi_cs);
		gpio_clear(gpio->fpga_cfg_creset);
		gpio_output(gpio->fpga_cfg_creset);
		gpio_input(gpio->fpga_cfg_cdone);
		gpio_input(gpio->max5864_select);
	}
#endif

	/* enable input on SCL and SDA pins */
	SCU_SFSI2C0 = SCU_I2C0_NOMINAL;
}

/* Run after pins_shutdown() and prior to enabling power supplies. */
void pins_setup(void)
{
	/* Detect Platform */
	const platform_gpio_t* gpio = platform_gpio();
	const platform_scu_t* scu = platform_scu();

	/* Configure LEDs */
	led_off(0);
	led_off(1);
	led_off(2);
#ifdef IS_FOUR_LEDS
	if (IS_FOUR_LEDS) {
		led_off(3);
	}
#endif

	gpio_output(gpio->led[0]);
	gpio_output(gpio->led[1]);
	gpio_output(gpio->led[2]);

#ifdef IS_FOUR_LEDS
	if (IS_FOUR_LEDS) {
		gpio_output(gpio->led[3]);
	}
#endif

	/* Configure drivers and driver pins */
#ifdef IS_PRALINE
	if (IS_PRALINE) {
		ssp_config_ice40_fpga.gpio_select = gpio->fpga_cfg_spi_cs;
		ice40.gpio_select = gpio->fpga_cfg_spi_cs;
		ice40.gpio_creset = gpio->fpga_cfg_creset;
		ice40.gpio_cdone = gpio->fpga_cfg_cdone;
	}
#endif

	jtag_gpio_cpld.gpio_tck = gpio->cpld_tck;

#ifdef IS_NOT_PRALINE
	if (IS_NOT_PRALINE) {
		jtag_gpio_cpld.gpio_tms = gpio->cpld_tms;
		jtag_gpio_cpld.gpio_tdi = gpio->cpld_tdi;
		jtag_gpio_cpld.gpio_tdo = gpio->cpld_tdo;
	}
#endif

#ifdef IS_EXPANSION_COMPATIBLE
	if (IS_EXPANSION_COMPATIBLE) {
		jtag_gpio_cpld.gpio_pp_tms = gpio->cpld_pp_tms;
		jtag_gpio_cpld.gpio_pp_tdo = gpio->cpld_pp_tdo;
	}
#endif

	mixer_bus_setup(&mixer);

	/* Configure external clock in */
	scu_pinmux(scu->PINMUX_GP_CLKIN, SCU_CLK_IN | SCU_CONF_FUNCTION1);
}

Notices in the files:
firmware/sgpio_passthrough_rom_to_ram/sgpio_passthrough.c:
Copyright 2012 Michael Ossmann
Copyright (C) 2012 Jared Boone
Copyright (C) 2012 Benjamin Vernoux
hardware/hackrf-one/hackrf-one.kicad_pcb:
Copyright 2012-2020 Great Scott Gadgets
Licensed under the CERN-OHL-P v2
hardware/operacake/operacake.kicad_pcb:
Copyright 2024 Great Scott Gadgets
License: GPL v2
